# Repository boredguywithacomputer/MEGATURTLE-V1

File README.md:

# MEGATURTLE-V1
An ESP32-S3 based custom drone flight controller that is a part of a bigger project. This is not the entire project, but is the only part that needs funding. 

<a href='https://epicturtle.web.app/demoflightcontroller/'>Here's a link to a demo</a><br>
<a href='https://epicturtle.web.app/schemm.pdf'>PDF version of schematic</a>

It features
- 4 connectors for each individual ESC of my quadcopter
  -  One ESC will supply 5v for the flight controller
- A voltage divider setup that enables measurement of the LiPo battery's voltage and capacity
- An ESP32-S3 Wroom-1 microcontroller
- An IMU consisting of Bosch's BMI270 + BMM150, and an BMP388 Barometer
- Sockets to mount an NRF24L01 module

Note:
DRC says the courtyard two header pins overlap with those of the ESP32's antenna, but I ignored it since I won't need wireless connectivity. 

# Schematic

# Board

<br>

# Bill Of Materials
|Component                  |Total Price ($)|Part #                                                           |Link                                                                     |Qty|JLCPCB Part #|
|---------------------------|---------------|-----------------------------------------------------------------|-------------------------------------------------------------------------|---|-------------|
|22uF                       |0.472          |CL10A226MQ8NRNC                                                  |https://jlcpcb.com/partdetail/60514-CL10A226MQ8NRNC/C59461               |20 |C59461       |
|1uF                        |0.284          |CL05A105KA5NQNC                                                  |https://jlcpcb.com/partdetail/53938-CL05A105KA5NQNC/C52923               |20 |C52923       |
|10uF                       |0.524          |CL10A106KP8NNNC                                                  |https://jlcpcb.com/partdetail/20411-CL10A106KP8NNNC/C19702               |20 |C19702       |
|0.1uF                      |0.0868         |CL05B104KO5NNNC                                                  |https://jlcpcb.com/partdetail/1877-CL05B104KO5NNNC/C1525                 |28 |C1525        |
|LED                        |0.144          |KT-0603R                                                         |https://jlcpcb.com/partdetail/Hubei_KENTOElec-KT0603R/C2286              |20 |C2286        |
|BMP388                     |4.7298         |BMP388                                                           |https://jlcpcb.com/partdetail/BoschSensortec-BMP388/C779278              |2  |C779278      |
|BMI270                     |6.501          |BMI270                                                           |https://jlcpcb.com/partdetail/BoschSensortec-BMI270/C2836813             |2  |C2836813     |
|USB_C_Receptacle_USB2.0_14P|0.3686         |TYPE-C-31-M-12                                                   |https://jlcpcb.com/partdetail/Korean_HropartsElec-TYPE_C_31_M12/C165948  |2  |C165948      |
|Conn_01x03_Pin             |7.0924         |TSM-103-01-L-SV                                                  |https://jlcpcb.com/partdetail/Samtec-TSM_103_01_LSV/C6886650             |14 |C6886650     |
|Conn_01x03_Pin             |               |                                                                 |                                                                         |   |             |
|NRF24L01                   |0.3618         |PM254-2-04-S-8.5                                                 |https://jlcpcb.com/partdetail/HCTL-PM254_2_04_S_85/C3975149              |2  |C3975149     |
|10K                        |0.024          |0402WGF1002TCE                                                   |https://jlcpcb.com/partdetail/26487-0402WGF1002TCE/C25744                |20 |C25744       |
|100K                       |0.022          |0402WGF1003TCE                                                   |https://jlcpcb.com/partdetail/26484-0402WGF1003TCE/C25741                |20 |C25741       |
|5.1K                       |0.018          |0402WGF5101TCE                                                   |https://jlcpcb.com/partdetail/26648-0402WGF5101TCE/C25905                |20 |C25905       |
|33K                        |0.016          |0402WGF3302TCE                                                   |https://jlcpcb.com/partdetail/26522-0402WGF3302TCE/C25779                |20 |C25779       |
|1K                         |0.022          |0402WGF1001TCE                                                   |https://jlcpcb.com/partdetail/12256-0402WGF1001TCE/C11702                |20 |C11702       |
|SW_Push                    |0.4416         |TS-1088-AR02016                                                  |https://jlcpcb.com/partdetail/XUNPU-TS_1088AR02016/C720477               |8  |C720477      |
|ESP32-S3-WROOM-1           |9.6078         |ESP32-S3-WROOM-1-N8                                              |https://jlcpcb.com/partdetail/3198296-ESP32_S3_WROOM_1N8/C2913198        |2  |C2913198     |
|AMS1117                    |0.3944         |AMS1117-3.3                                                      |https://jlcpcb.com/partdetail/Advanced_MonolithicSystems-AMS1117_33/C6186|2  |C6186        |
|BMM150                     |3.1424         |BMM150                                                           |https://jlcpcb.com/partdetail/BoschSensortec-BMM150/C171681              |2  |C171681      |
|PCB Price                  |7              |                                                                 |                                                                         |   |             |
|Standard PCBA Setup        |25.56          |*board must be standard pcba because of some components I'm using|                                                                         |   |             |
|Stencil                    |8.21           |                                                                 |                                                                         |   |             |
|Total                      |75.0226        |                                                                 |                                                                         |   |             |

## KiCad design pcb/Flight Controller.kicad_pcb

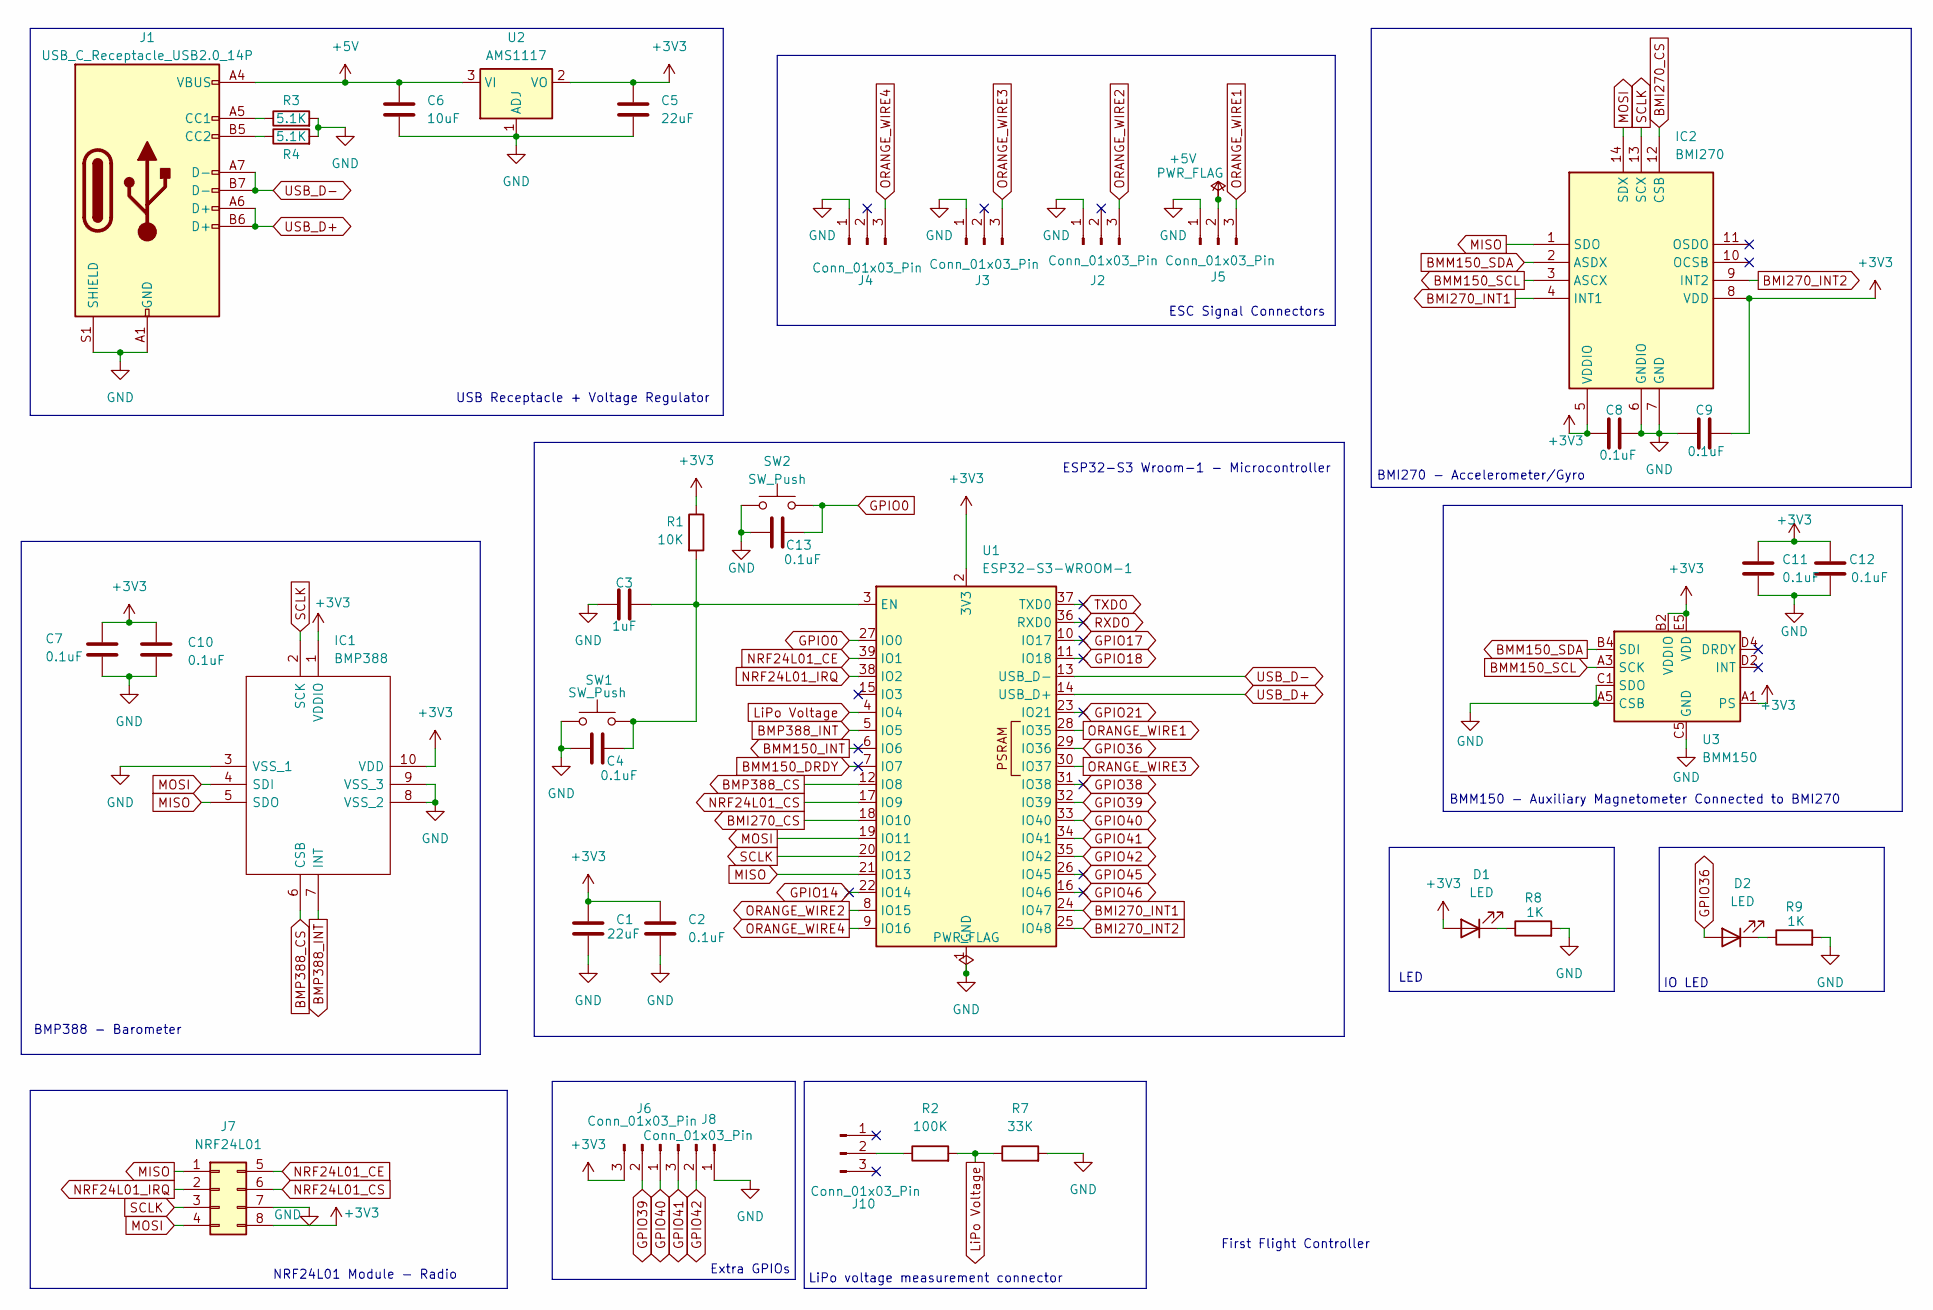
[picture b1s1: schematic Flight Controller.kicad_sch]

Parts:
C1, C5: 22uF; C_0603_1608Metric
C2, C4, C7, C8, C9, C10, C11, C12, C13: 0.1uF; C_0402_1005Metric
C3: 1uF; C_0402_1005Metric
C6: 10uF; C_0603_1608Metric
D1, D2: LED; LED_0603_1608Metric
IC1: BMP388; Manufacturer_Part_Number BMP388
IC2: BMI270; Manufacturer_Part_Number BMI270; Mouser Part Number 262-BMI270
J1: USB_C_Receptacle_USB2.0_14P; USB_C_Receptacle_HRO_TYPE-C-31-M-12
J2, J3, J4, J5, J6, J8: Conn_01x03_Pin; PinHeader_1x03_P2.54mm_Vertical_SMD_Pin1Left
J7: NRF24L01; PinSocket_2x04_P2.54mm_Vertical_SMD
J10: Conn_01x03_Pin; PinSocket_1x03_P2.54mm_Vertical_SMD_Pin1Left
R1: 10K; R_0402_1005Metric
R2: 100K; R_0402_1005Metric
R3, R4: 5.1K; R_0402_1005Metric
R7: 33K; R_0402_1005Metric
R8, R9: 1K; R_0402_1005Metric
SW1, SW2: SW_Push; SW_Push_SPST_NO_Alps_SKRK
U1: ESP32-S3-WROOM-1
U2: AMS1117; SOT-223-3_TabPin2
U3: BMM150; WLCSP-12_1.56x1.56mm_P0.4mm

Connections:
+3V3: C1.1, C2.1, C5.1, C7.1, C8.1, C9.2, C10.1, C11.1, C12.1, D1.2 (A), IC1.1 (VDDIO), IC1.10 (VDD), IC2.5 (VDDIO), IC2.8 (VDD), J6.3, J7.8, R1.1, U1.2 (3V3), U2.2 (VO), U3.A1 (PS), U3.B2 (VDDIO), U3.E5 (VDD)
+5V: C6.1, J1.A4 (VBUS), J1.A9 (VBUS), J1.B4 (VBUS), J1.B9 (VBUS), J5.2, U2.3 (VI)
BMI270_CS: IC2.12 (CSB), U1.18 (IO10)
BMI270_INT1: IC2.4 (INT1), U1.24 (IO47)
BMI270_INT2: IC2.9 (INT2), U1.25 (IO48)
BMM150_DRDY: U1.7 (IO7)
BMM150_INT: U1.6 (IO6)
BMM150_SCL: IC2.3 (ASCX), U3.A3 (SCK)
BMM150_SDA: IC2.2 (ASDX), U3.B4 (SDI)
BMP388_CS: IC1.6 (CSB), U1.12 (IO8)
BMP388_INT: IC1.7 (INT), U1.5 (IO5)
GND: C1.2, C2.2, C3.1, C4.1, C5.2, C6.2, C7.2, C8.2, C9.1, C10.2, C11.2, C12.2, C13.1, IC1.3 (VSS_1), IC1.8 (VSS_2), IC1.9 (VSS_3), IC2.6 (GNDIO), IC2.7 (GND), J1.A1 (GND), J1.A12 (GND), J1.B1 (GND), J1.B12 (GND), J1.S1 (SHIELD), J2.1, J3.1, J4.1, J5.1, J7.7, J8.1, R3.2, R4.2, R7.2, R8.2, R9.2, SW1.1, SW2.1, U1.1 (GND), U1.40 (GND), U1.41 (GND), U2.1 (ADJ), U3.A5 (CSB), U3.C1 (SDO), U3.C5 (GND), U3.E1 (GND), U3.E3 (GND)
GPIO0: C13.2, SW2.2, U1.27 (IO0)
GPIO14: U1.22 (IO14)
GPIO17: U1.10 (IO17)
GPIO18: U1.11 (IO18)
GPIO21: U1.23 (IO21)
GPIO36: D2.2 (A), U1.29 (IO36)
GPIO38: U1.31 (IO38)
GPIO39: J6.2, U1.32 (IO39)
GPIO40: J6.1, U1.33 (IO40)
GPIO41: J8.3, U1.34 (IO41)
GPIO42: J8.2, U1.35 (IO42)
GPIO45: U1.26 (IO45)
GPIO46: U1.16 (IO46)
LiPo Voltage: R2.2, R7.1, U1.4 (IO4)
MISO: IC1.5 (SDO), IC2.1 (SDO), J7.1, U1.21 (IO13)
MOSI: IC1.4 (SDI), IC2.14 (SDX), J7.4, U1.19 (IO11)
NRF24L01_CE: J7.5, U1.39 (IO1)
NRF24L01_CS: J7.6, U1.17 (IO9)
NRF24L01_IRQ: J7.2, U1.38 (IO2)
unnamed: D1.1 (K), R8.1
unnamed: D2.1 (K), R9.1
unnamed: J1.A5 (CC1), R3.1
unnamed: J1.B5 (CC2), R4.1
unnamed: J10.2, R2.1
unnamed: C3.2, C4.2, R1.2, SW1.2, U1.3 (EN)
ORANGE_WIRE1: J5.3, U1.28 (IO35)
ORANGE_WIRE2: J2.3, U1.8 (IO15)
ORANGE_WIRE3: J3.3, U1.30 (IO37)
ORANGE_WIRE4: J4.3, U1.9 (IO16)
RXDO: U1.36 (RXD0)
SCLK: IC1.2 (SCK), IC2.13 (SCX), J7.3, U1.20 (IO12)
TXDO: U1.37 (TXD0)
USB_D+: J1.A6 (D+), J1.B6 (D+), U1.14 (USB_D+)
USB_D-: J1.A7 (D-), J1.B7 (D-), U1.13 (USB_D-)

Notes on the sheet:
USB Receptacle + Voltage Regulator
BMM150 - Auxiliary Magnetometer Connected to BMI270
LED
LiPo voltage measurement connector
NRF24L01 Module - Radio
BMP388 - Barometer
Extra GPIOs
First Flight Controller
BMI270 - Accelerometer/Gyro
ESC Signal Connectors
ESP32-S3 Wroom-1 - Microcontroller
IO LED

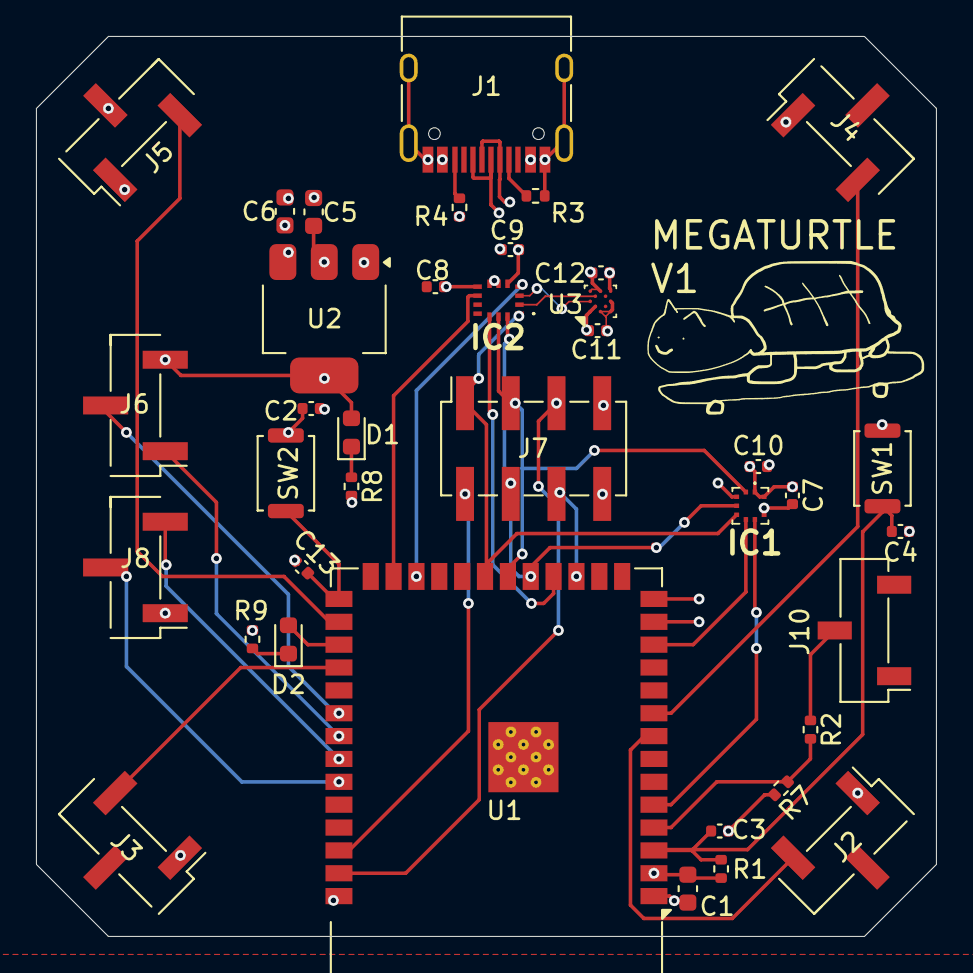
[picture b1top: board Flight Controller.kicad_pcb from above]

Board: 4 copper layers, 50.0 x 50.0 mm, 38 parts (0 on the bottom side), 35 nets.

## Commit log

2026-06-19 fixed grammar
    changed "A" to "An" one time.
2026-06-20 added stuff
    yea
2026-06-20 Add Bill of Materials to README
    Added a Bill of Materials section with component details and pricing.
